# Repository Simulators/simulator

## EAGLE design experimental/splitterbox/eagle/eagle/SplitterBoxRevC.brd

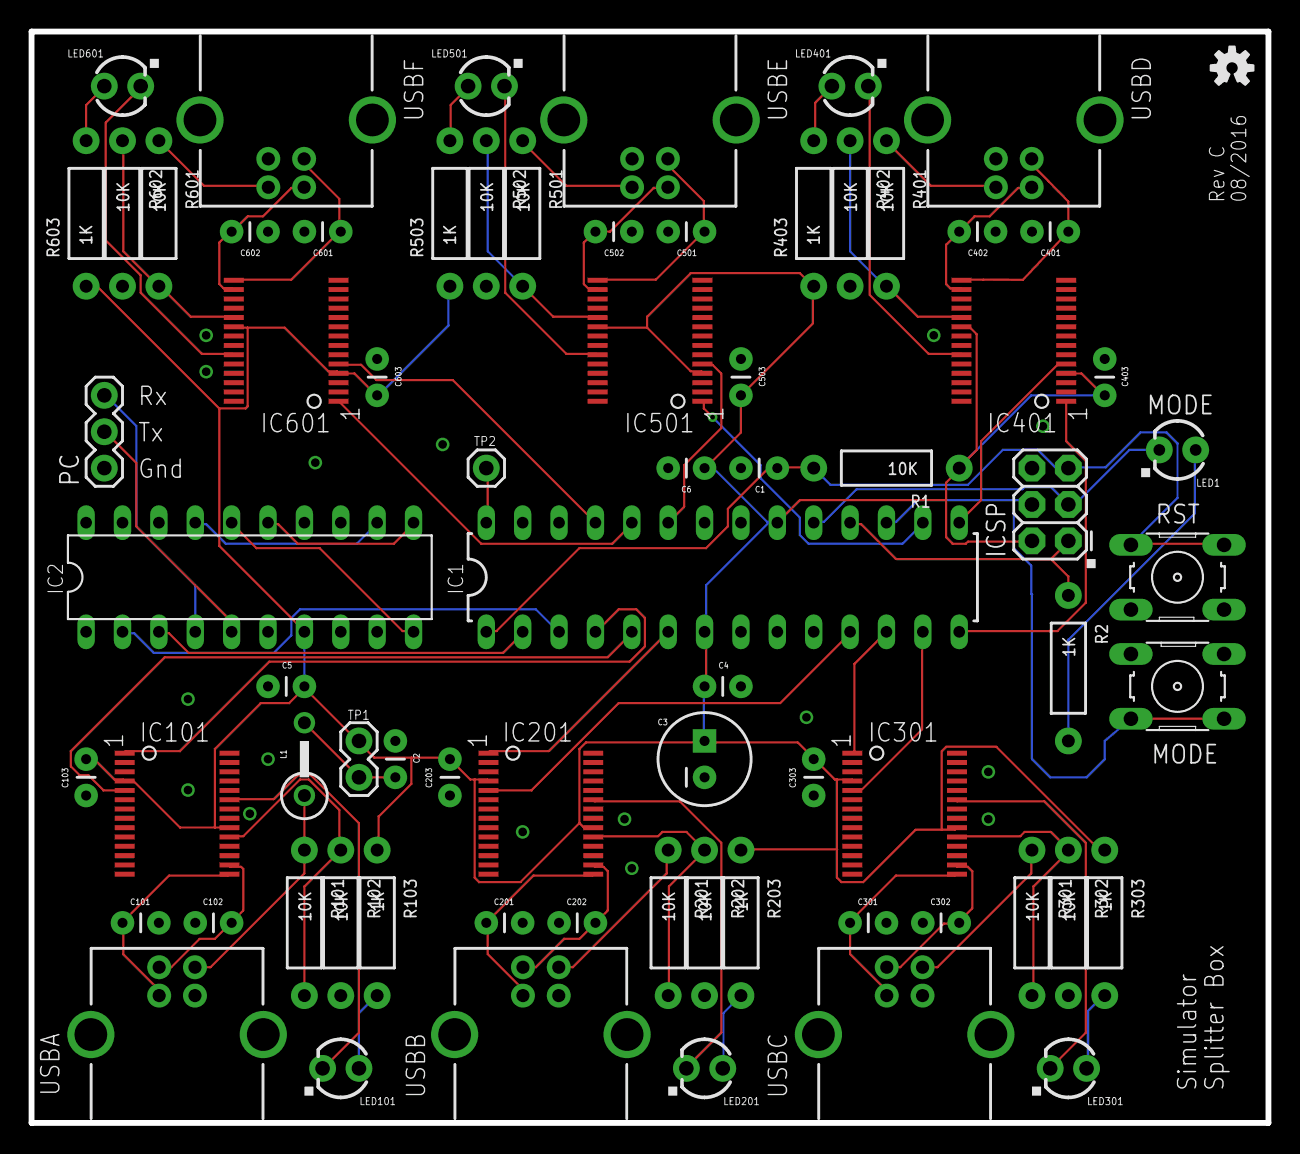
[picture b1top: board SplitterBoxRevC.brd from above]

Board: 2 copper layers, 86.4 x 76.2 mm, 73 parts (0 on the bottom side), 64 nets.

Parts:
C1, C4, C5, C6, C103, C203, C303, C403, C503, C603: 100nF; CAP-PTH-SMALL
C2: 10nF; CAP-PTH-SMALL
C3: 47uF; CPOL-RADIAL-100UF-25V
C101, C102, C201, C202, C301, C302, C401, C402, C501, C502, C601, C602: 47pF; CAP-PTH-SMALL
IC1: ATMEGA328P_PDIP; DIL28-3
IC2: MAX233; DIL20
IC101, IC201, IC301, IC401, IC501, IC601: FT232RL; SSOP28DB
ICSP: AVR_SPI_PRG_6PTH; 2X3
L1: BL02RN1
LED1: LED-2COLOUR; LED3MM
LED101, LED201, LED301, LED401, LED501, LED601: Yellow; LED3MM_LARGEHOLES
LOGO1: OSHW-LOGOS; OSHW-LOGO-S
MODE: B3F-10XX
PC: 1X03
R1, R101, R102, R201, R202, R301, R302, R401, R402, R501, R502, R601, R602: 10K; AXIAL-0.4
R2, R103, R203, R303, R403, R503, R603: 1K; AXIAL-0.4
RST: B3F-10XX
TP1: M02PTH; 1X02
TP2: 1X01
USBA: USB-B; USB-B-PTH
USBB: USB-B; USB-B-PTH
USBC: USB-B; USB-B-PTH
USBD: USB-B; USB-B-PTH
USBE: USB-B; USB-B-PTH
USBF: USB-B; USB-B-PTH

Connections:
CRO: IC1.28, TP2.1
GND: C1.2, C2.1, C3.2, C4.2, C5.2, C6.2, C101.2, C102.2, C103.2, C201.2, C202.2, C203.2, C301.2, C302.2, C303.2, C401.2, C402.2, C403.2, C501.2, C502.2, C503.2, C601.2, C602.2, C603.2, IC1.8, IC1.22, IC2.6, IC2.9, IC101.7, IC101.18, IC101.21, IC101.25, IC101.26, IC201.7, IC201.18, IC201.21, IC201.25, IC201.26, IC301.7, IC301.18, IC301.21, IC301.25, IC301.26, IC401.7, IC401.18, IC401.21, IC401.25, IC401.26, IC501.7, IC501.18, IC501.21, IC501.25, IC501.26, IC601.7, IC601.18, IC601.21, IC601.25, IC601.26, ICSP.6, MODE.3, MODE.4, PC.1, R102.P$2, R202.P$2, R302.P$2, R402.P$2, R502.P$2, R602.P$2, RST.3, RST.4, USBA.GND, USBB.GND, USBC.GND, USBD.GND, USBE.GND, USBF.GND
MISO: IC1.18, ICSP.1, R2.P$1
MOSI: IC1.17, ICSP.4, MODE.1, MODE.2
unnamed: C201.1, IC201.15, USBB.D+
unnamed: C202.1, IC201.16, USBB.D-
unnamed: IC201.19, R201.P$2, R202.P$1
unnamed: LED201.A, R203.P$2
unnamed: IC201.23, LED201.K
unnamed: C401.1, IC401.15, USBD.D+
unnamed: C402.1, IC401.16, USBD.D-
unnamed: IC2.10, IC2.16
unnamed: C2.2, L1.2, TP1.2
unnamed: IC2.11, IC2.15
unnamed: IC2.12, IC2.17
unnamed: IC401.19, R401.P$2, R402.P$1
unnamed: LED401.A, R403.P$2
unnamed: IC401.23, LED401.K
unnamed: C301.1, IC301.15, USBC.D+
unnamed: C302.1, IC301.16, USBC.D-
unnamed: R201.P$1, USBB.VBUS
unnamed: IC301.19, R301.P$2, R302.P$1
unnamed: LED301.A, R303.P$2
unnamed: IC301.23, LED301.K
unnamed: R301.P$1, USBC.VBUS
unnamed: C101.1, IC101.15, USBA.D+
unnamed: C102.1, IC101.16, USBA.D-
unnamed: IC101.19, R101.P$2, R102.P$1
unnamed: LED101.A, R103.P$2
unnamed: IC101.23, LED101.K
unnamed: R401.P$1, USBD.VBUS
unnamed: C501.1, IC501.15, USBE.D+
unnamed: C502.1, IC501.16, USBE.D-
unnamed: IC501.19, R501.P$2, R502.P$1
unnamed: LED501.A, R503.P$2
unnamed: IC501.23, LED501.K
unnamed: R501.P$1, USBE.VBUS
unnamed: C601.1, IC601.15, USBF.D+
unnamed: C602.1, IC601.16, USBF.D-
unnamed: IC601.19, R601.P$2, R602.P$1
unnamed: LED601.A, R603.P$2
unnamed: IC601.23, LED601.K
unnamed: R601.P$1, USBF.VBUS
unnamed: LED1.A, R2.P$2
RESET: C1.1, IC1.1, ICSP.5, R1.P$2, RST.1, RST.2
RX: IC2.4, PC.3
RXA: IC1.5, IC101.5
RXB: IC1.11, IC201.5
RXC: IC1.13, IC301.5
RXD: IC1.15, IC401.5
RXE: IC1.23, IC501.5
RXF: IC1.25, IC601.5
RXS: IC1.2, IC2.3
SCK: IC1.19, ICSP.3, LED1.K
TX: IC2.5, PC.2
TXA: IC1.4, IC101.1
TXB: IC1.6, IC201.1
TXC: IC1.12, IC301.1
TXD: IC1.14, IC401.1
TXE: IC1.16, IC501.1
TXF: IC1.24, IC601.1
TXS: IC1.3, IC2.2
VBUSA: L1.1, R101.P$1, USBA.VBUS
VCC: C3.1, C4.1, C5.1, C6.1, C103.1, C203.1, C303.1, C403.1, C503.1, C603.1, IC1.7, IC1.20, IC2.7, IC101.4, IC101.20, IC201.4, IC201.20, IC301.4, IC301.20, IC401.4, IC401.20, IC501.4, IC501.20, IC601.4, IC601.20, ICSP.2, R1.P$1, R103.P$1, R203.P$1, R303.P$1, R403.P$1, R503.P$1, R603.P$1, TP1.1

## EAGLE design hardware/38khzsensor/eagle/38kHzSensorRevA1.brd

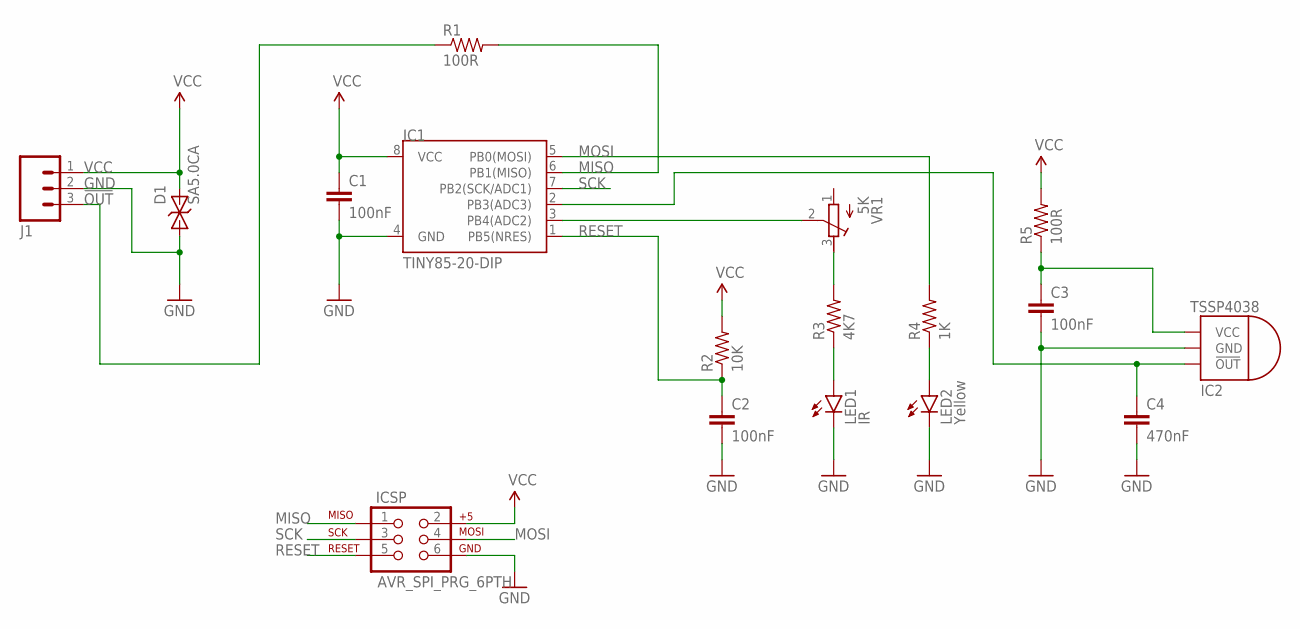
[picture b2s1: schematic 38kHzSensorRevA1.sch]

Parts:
C1, C2, C3: 100nF; CAP-PTH-SMALL
C4: 470nF; CAP-PTH-5MM
D1: SA5.0CA; DO41_TVS
IC1: TINY85-20-DIP; DIP08
IC2: TSSP4038EDGE; TSSP4038_PKG_EDGE
ICSP: AVR_SPI_PRG_6PTH; 2X3
J1: M03PTH; 1X03
LED1: IR; LED5MM
LED2: Yellow; LED3MM
R1, R5: 100R; AXIAL-0.4
R2: 10K; AXIAL-0.4
R3: 4K7; AXIAL-0.4
R4: 1K; AXIAL-0.4
VR1: 5K; RTRIM3296X

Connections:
!OUT: J1.3, R1.P$1 (1)
GND: C1.2, C2.2, C3.2, C4.2, D1.A, IC1.4 (GND), IC2.GND, ICSP.6, J1.2, LED1.K (C), LED2.K (C)
MISO: IC1.6 (PB1(MISO)), ICSP.1, R1.P$2 (2)
MOSI: IC1.5 (PB0(MOSI)), ICSP.4, R4.P$2 (2)
unnamed: IC1.3 (PB4(ADC2)), VR1.2 (S)
unnamed: R3.P$2 (2), VR1.3 (E)
unnamed: C4.1, IC1.2 (PB3(ADC3)), IC2.OUT (!OUT)
unnamed: C3.1, IC2.VCC, R5.P$1 (1)
unnamed: LED1.A, R3.P$1 (1)
unnamed: LED2.A, R4.P$1 (1)
RESET: C2.1, IC1.1 (PB5(NRES)), ICSP.5, R2.P$1 (1)
SCK: IC1.7 (PB2(SCK/ADC1)), ICSP.3
VCC: C1.1, D1.C, IC1.8 (VCC), ICSP.2, J1.1, R2.P$2 (2), R5.P$2 (2)

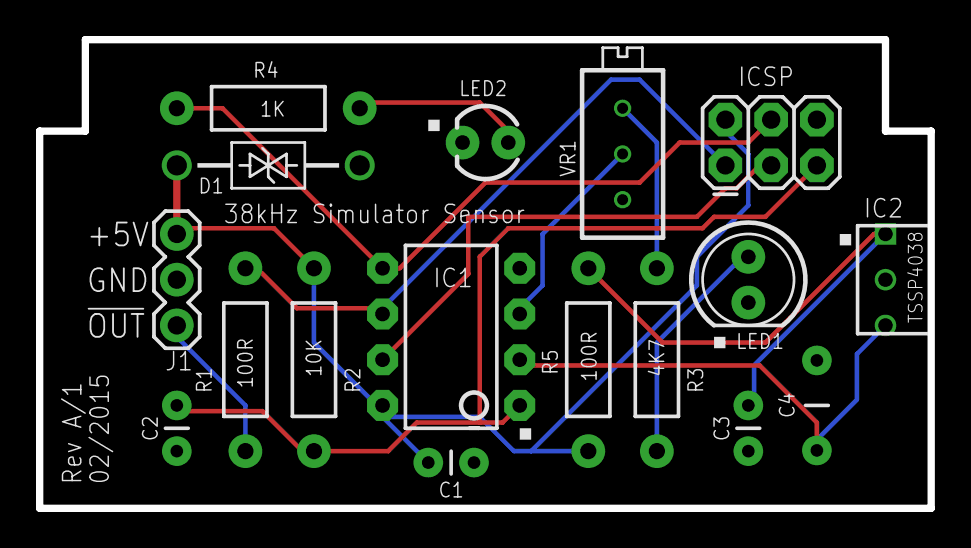
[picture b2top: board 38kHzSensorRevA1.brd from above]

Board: 2 copper layers, 49.5 x 26.0 mm, 17 parts (0 on the bottom side), 13 nets.

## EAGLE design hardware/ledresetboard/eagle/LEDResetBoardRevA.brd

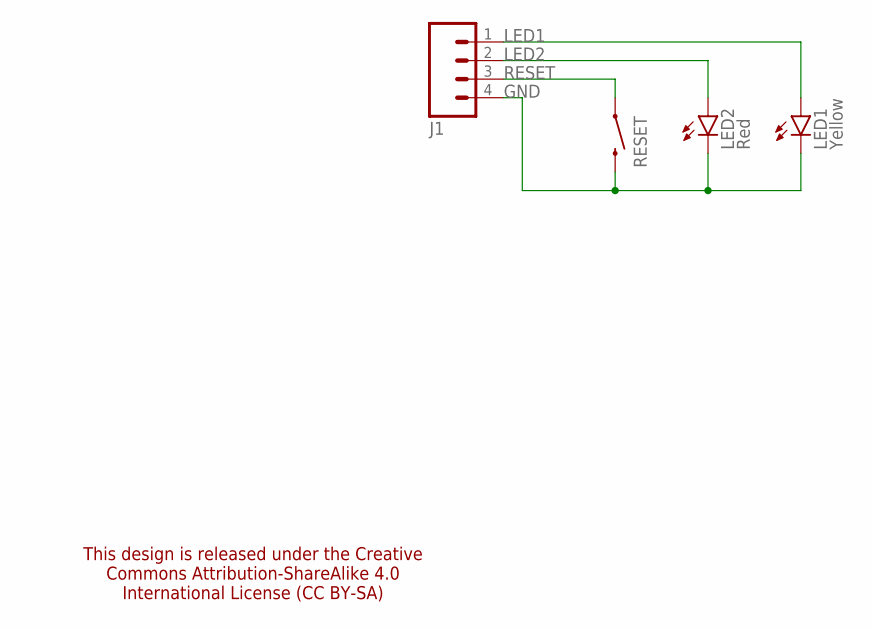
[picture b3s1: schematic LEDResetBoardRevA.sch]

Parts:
J1: M04PTH; 1X04
LED1: Yellow; LED3MM
LED2: Red; LED3MM
RESET: SWITCH-MOMENTARY-2PTH; TACTILE-PTH

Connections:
GND: J1.4, LED1.K (C), LED2.K (C), RESET.3 (2)
LED1: J1.1, LED1.A
LED2: J1.2, LED2.A
RESET: J1.3, RESET.1

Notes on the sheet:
This design is released under the Creative Commons Attribution-ShareAlike 4.0 International License (CC BY-SA)

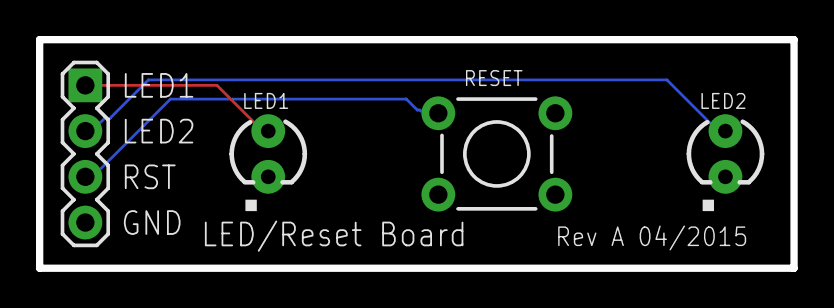
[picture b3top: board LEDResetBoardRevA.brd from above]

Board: 2 copper layers, 41.9 x 12.7 mm, 4 parts (0 on the bottom side), 4 nets.

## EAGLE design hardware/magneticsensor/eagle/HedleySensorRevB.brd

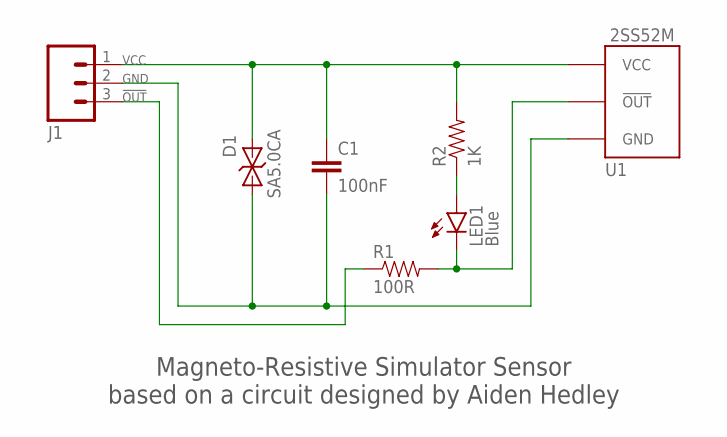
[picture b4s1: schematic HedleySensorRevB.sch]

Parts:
C1: 100nF; CAP-PTH-SMALL
D1: SA5.0CA; DO41_TVS
J1: M03PTH; 1X03
LED1: Blue; LED3MM
R1: 100R; AXIAL-0.4
R2: 1K; AXIAL-0.4
U1: 2SS52MFLAT; 2SS52M_FLAT

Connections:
!OUT: J1.3, R1.P$1 (1)
GND: C1.2, D1.A, J1.2, U1.P$1 (GND)
unnamed: LED1.K (C), R1.P$2 (2), U1.P$2 (!OUT!)
unnamed: LED1.A, R2.P$1 (1)
VCC: C1.1, D1.C, J1.1, R2.P$2 (2), U1.P$3 (VCC)

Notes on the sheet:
Magneto-Resistive Simulator Sensor based on a circuit designed by Aiden Hedley

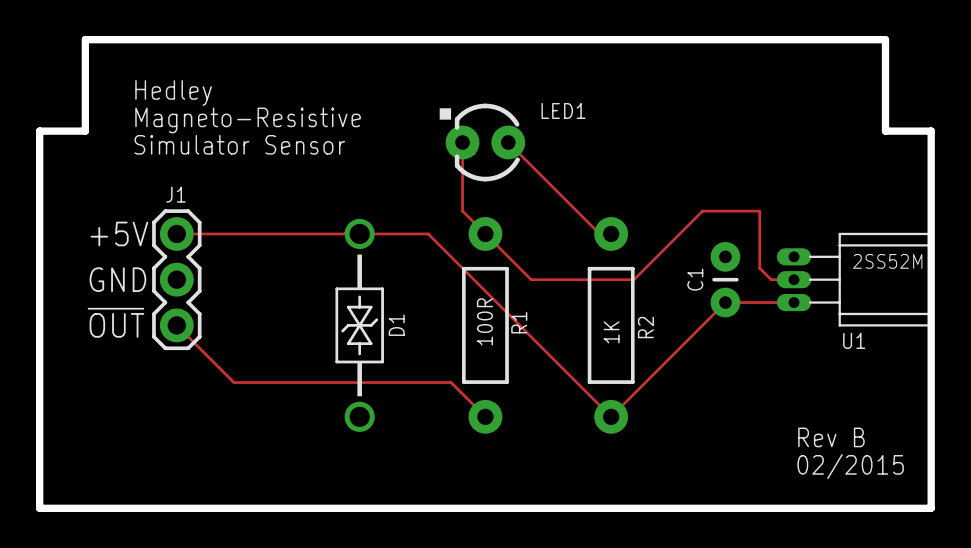
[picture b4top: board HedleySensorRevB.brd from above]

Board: 2 copper layers, 49.5 x 26.0 mm, 7 parts (0 on the bottom side), 5 nets.

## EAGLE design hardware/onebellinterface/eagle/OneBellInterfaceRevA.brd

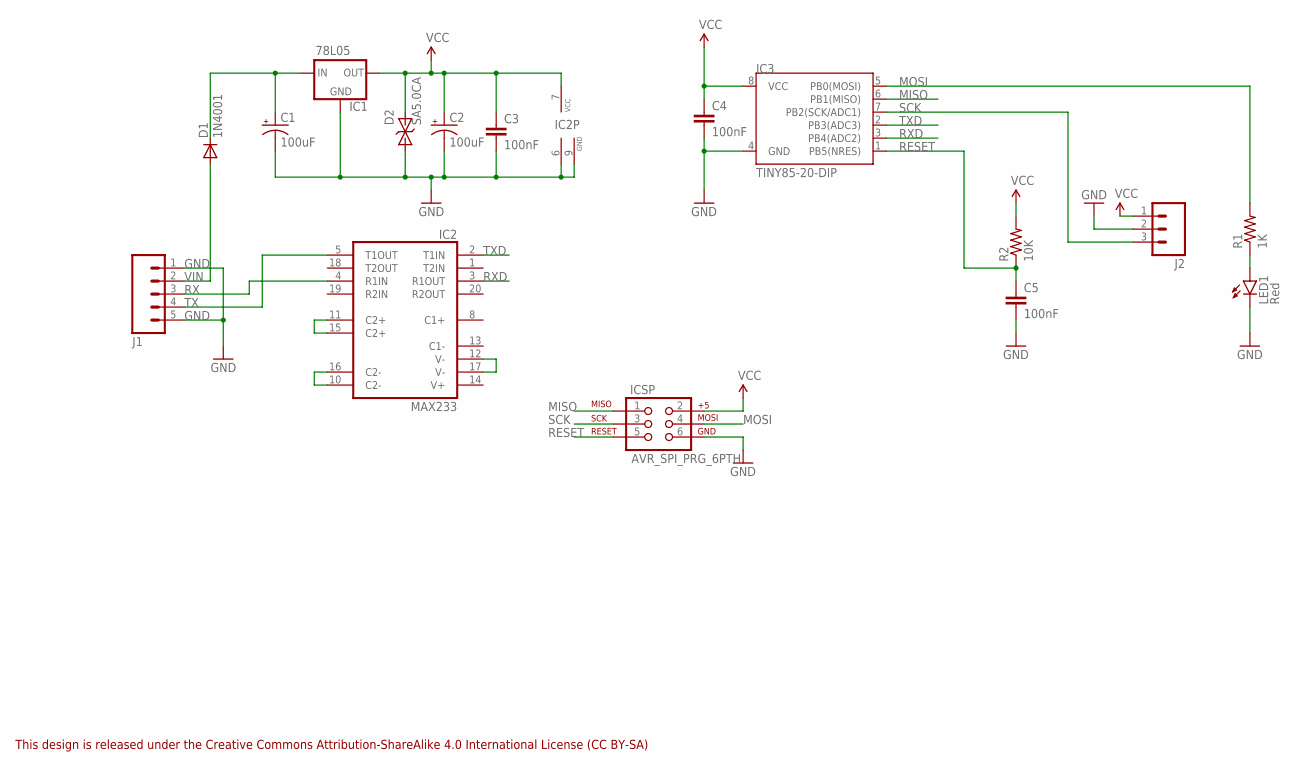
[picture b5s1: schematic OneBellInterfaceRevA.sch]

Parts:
C1, C2: 100uF; CPOL-RADIAL-100UF-25V
C3, C4, C5: 100nF; CAP-PTH-SMALL
D1: 1N4001; DO41_DIODE
D2: SA5.0CA; DO41_TVS
IC1: 78L05; TO-92
IC2: MAX233; DIL20
IC3: TINY85-20-DIP; DIL08
ICSP: AVR_SPI_PRG_6PTH; 2X3
J1: M05PTH; 1X05
J2: M03PTH; 1X03
LED1: Red; LED3MM
R1: 1K; AXIAL-0.4
R2: 10K; AXIAL-0.4

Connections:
GND: C1.2 (-), C2.2 (-), C3.2, C4.2, C5.2, D2.A, IC1.2 (GND), IC2.6 (GND), IC2.9 (GND), IC3.4 (GND), ICSP.6, J1.1, J1.5, J2.2, LED1.K (C)
MISO: IC3.6 (PB1(MISO)), ICSP.1
MOSI: IC3.5 (PB0(MOSI)), ICSP.4, R1.P$2 (2)
unnamed: C1.1 (+), D1.C, IC1.3 (IN)
unnamed: LED1.A, R1.P$1 (1)
unnamed: IC2.11 (C2+), IC2.15 (C2+)
unnamed: IC2.10 (C2-), IC2.16 (C2-)
unnamed: IC2.12 (V-), IC2.17 (V-)
RESET: C5.1, IC3.1 (PB5(NRES)), ICSP.5, R2.P$1 (1)
RX: IC2.4 (R1IN), J1.3
RXD: IC2.3 (R1OUT), IC3.3 (PB4(ADC2))
SCK: IC3.7 (PB2(SCK/ADC1)), ICSP.3, J2.3
TX: IC2.5 (T1OUT), J1.4
TXD: IC2.2 (T1IN), IC3.2 (PB3(ADC3))
VCC: C2.1 (+), C3.1, C4.1, D2.C, IC1.1 (OUT), IC2.7 (VCC), IC3.8 (VCC), ICSP.2, J2.1, R2.P$2 (2)
VIN: D1.A, J1.2

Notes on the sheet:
This design is released under the Creative Commons Attribution-ShareAlike 4.0 International License (CC BY-SA)

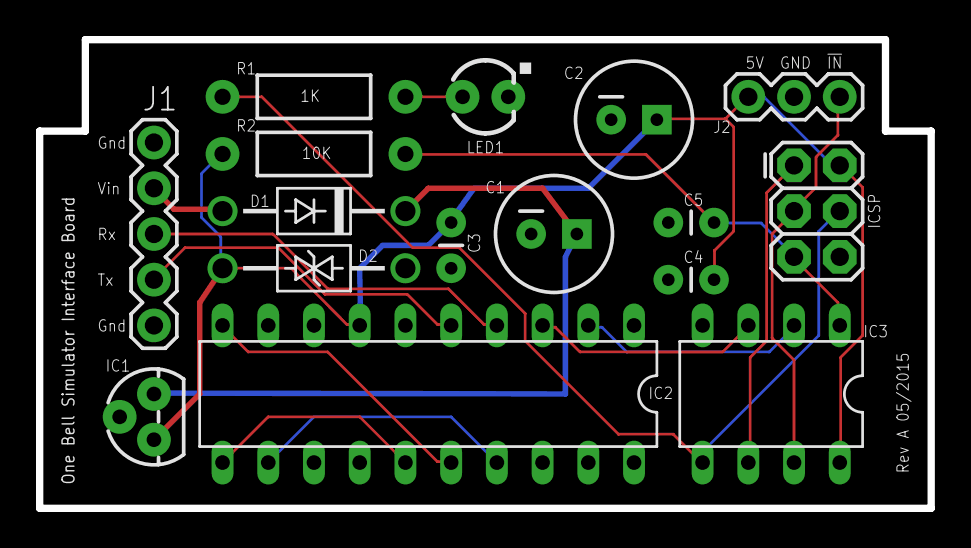
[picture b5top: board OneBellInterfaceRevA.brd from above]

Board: 2 copper layers, 49.5 x 26.0 mm, 16 parts (0 on the bottom side), 16 nets.

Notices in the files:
parts and their libraries:
SparkFun-DigitalIC: Licensing: Creative Commons ShareAlike 4.0 International - https://creativecommons.org/licenses/by-sa/4.0
